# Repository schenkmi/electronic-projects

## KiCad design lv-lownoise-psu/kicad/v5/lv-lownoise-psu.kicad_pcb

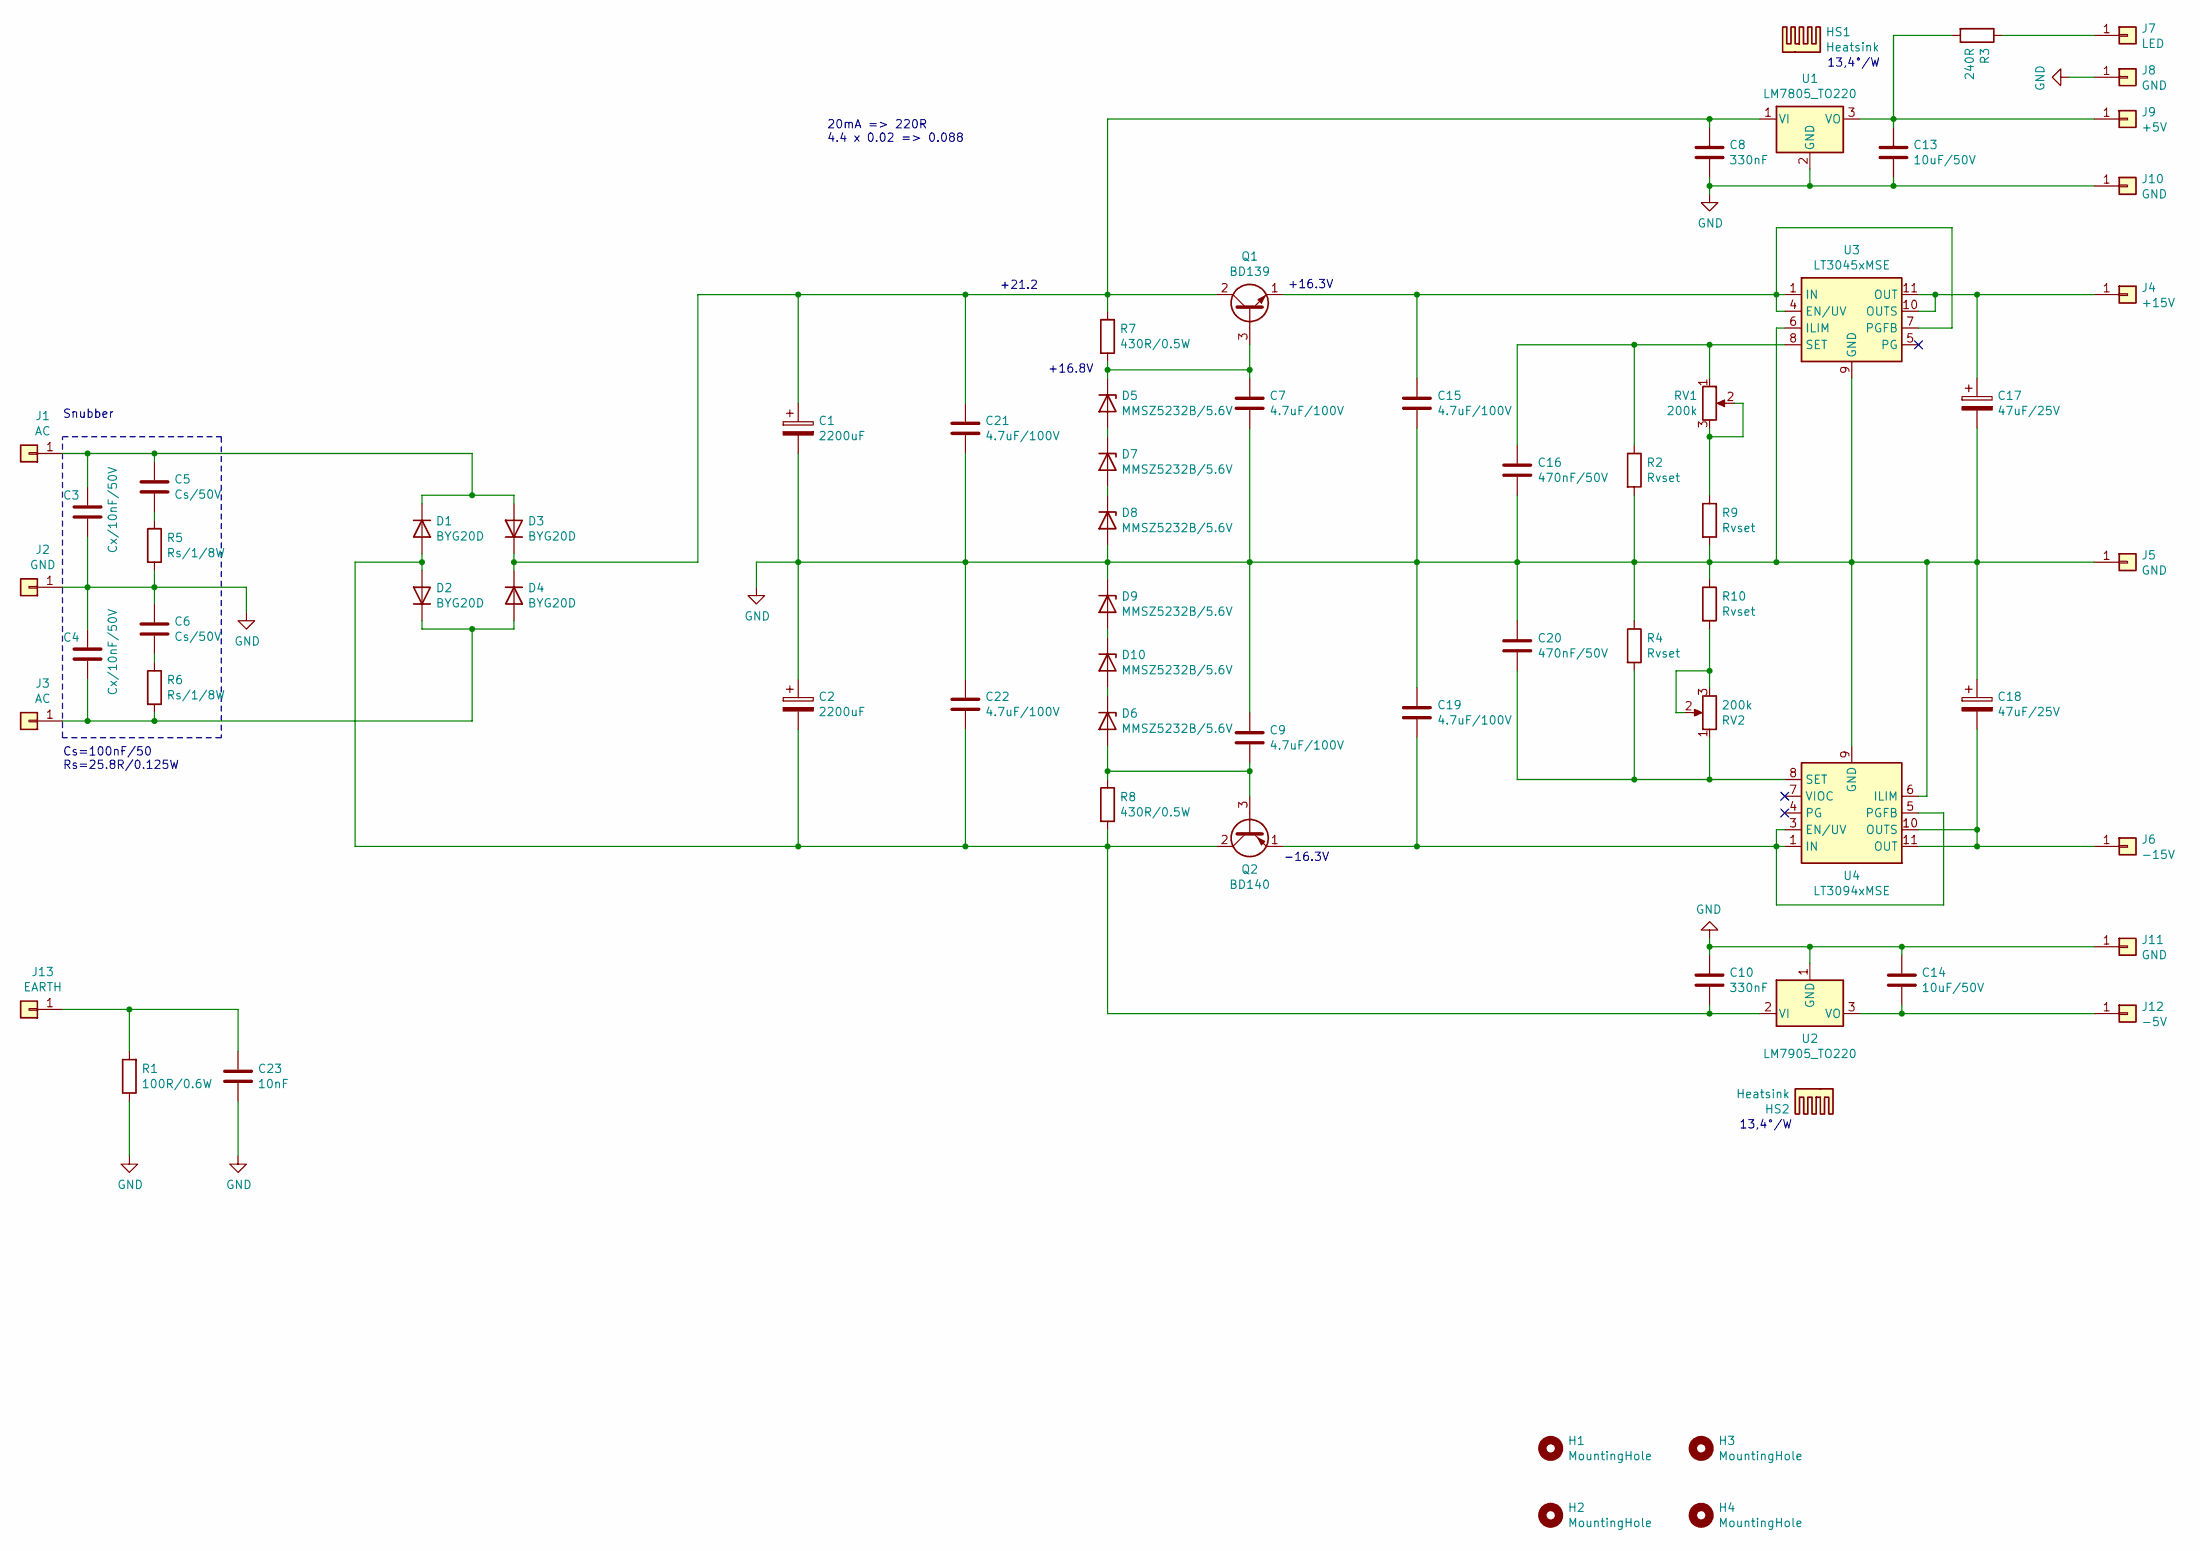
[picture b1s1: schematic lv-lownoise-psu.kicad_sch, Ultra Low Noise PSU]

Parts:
C1, C2: 2200uF; CP_Radial_D16.0mm_P7.50mm
C3, C4: Cx/10nF/50V; C_0805_2012Metric_Pad1.18x1.45mm_HandSolder
C5, C6: Cs/50V; C_0805_2012Metric_Pad1.18x1.45mm_HandSolder
C7, C9, C15, C19, C21, C22: 4.7uF/100V; C_1206_3216Metric_Pad1.33x1.80mm_HandSolder
C8, C10: 330nF; C_0805_2012Metric_Pad1.18x1.45mm_HandSolder
C13, C14: 10uF/50V; C_1210_3225Metric_Pad1.33x2.70mm_HandSolder
C16, C20: 470nF/50V; C_0805_2012Metric_Pad1.18x1.45mm_HandSolder
C17, C18: 47uF/25V; CP_EIA-7343-31_Kemet-D_HandSolder
C23: 10nF; C_Rect_L7.2mm_W2.5mm_P5.00mm_FKS2_FKP2_MKS2_MKP2
D1, D2, D3, D4: BYG20D; D_SMA_Handsoldering
D5, D6, D7, D8, D9, D10: MMSZ5232B/5.6V; D_SOD-123
H1, H2, H3, H4: MountingHole; MountingHole_3.2mm_M3_Pad_Via
HS1, HS2: Heatsink; Heatsink_Fischer_SK104-STC-STIC_35x13mm_2xDrill2.5mm
J1, J3: AC; Pin_D1.3mm_L11.0mm
J2: GND; Pin_D1.3mm_L11.0mm
J4: +15V; Pin_D1.0mm_L10.0mm
J5, J8, J10, J11: GND; Pin_D1.0mm_L10.0mm
J6: -15V; Pin_D1.0mm_L10.0mm
J7: LED; Pin_D1.0mm_L10.0mm
J9: +5V; Pin_D1.0mm_L10.0mm
J12: -5V; Pin_D1.0mm_L10.0mm
J13: EARTH; Pin_D1.3mm_L11.0mm
Q1: BD139; TO-126-3_Vertical
Q2: BD140; TO-126-3_Vertical
R1: 100R/0.6W; R_Axial_DIN0207_L6.3mm_D2.5mm_P10.16mm_Horizontal
R2, R4, R9, R10: Rvset; R_0805_2012Metric_Pad1.20x1.40mm_HandSolder
R3: 240R; R_0805_2012Metric_Pad1.20x1.40mm_HandSolder
R5, R6: Rs/1/8W; R_0805_2012Metric_Pad1.20x1.40mm_HandSolder
R7, R8: 430R/0.5W; R_0805_2012Metric_Pad1.20x1.40mm_HandSolder
RV1, RV2: 200k; Potentiometer_Bourns_3296W_Vertical
U1: LM7805_TO220; TO-220-3_Vertical
U2: LM7905_TO220; TO-220-3_Vertical
U3: LT3045xMSE; MSOP-12-1EP_3x4.039mm_P0.65mm_EP1.651x2.845mm
U4: LT3094xMSE; MSOP-12-1EP_3x4.039mm_P0.65mm_EP1.651x2.845mm

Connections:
GND: C1.2, C2.1, C3.2, C4.1, C6.1, C7.2, C8.2, C9.1, C10.1, C13.2, C14.1, C15.2, C16.2, C17.2, C18.1, C19.1, C20.1, C21.2, C22.1, C23.2, D8.2 (A), D9.1 (K), J2.1, J5.1, J8.1, J10.1, J11.1, R1.1, R2.2, R4.1, R5.2, R9.2, R10.1, U1.2 (GND), U2.1 (GND), U3.6 (ILIM), U3.9 (GND), U3.13 (GND), U4.6 (ILIM), U4.9 (GND)
unnamed: C5.2, R5.1
unnamed: C6.2, R6.1
unnamed: C2.2, C10.2, C22.2, D1.2 (A), D2.2 (A), Q2.2 (C), R8.2, U2.2 (VI)
unnamed: C3.1, C5.1, D1.1 (K), D3.2 (A), J1.1
unnamed: C4.2, D2.1 (K), D4.2 (A), J3.1, R6.2
unnamed: C1.1, C8.1, C21.1, D3.1 (K), D4.1 (K), Q1.2 (C), R7.1, U1.1 (VI)
unnamed: D5.2 (A), D7.1 (K)
unnamed: C7.1, D5.1 (K), Q1.3 (B), R7.2
unnamed: C9.2, D6.2 (A), Q2.3 (B), R8.1
unnamed: D7.2 (A), D8.1 (K)
unnamed: D6.1 (K), D10.2 (A)
unnamed: D9.2 (A), D10.1 (K)
unnamed: C17.1, J4.1, U3.10 (OUTS), U3.11 (OUT), U3.12 (OUT)
unnamed: C18.2, J6.1, U4.10 (OUTS), U4.11 (OUT), U4.12 (OUT)
unnamed: J7.1, R3.1
unnamed: C13.1, J9.1, R3.2, U1.3 (VO)
unnamed: C14.2, J12.1, U2.3 (VO)
unnamed: C23.1, J13.1, R1.2
unnamed: C15.1, Q1.1 (E), U3.1 (IN), U3.2 (IN), U3.3 (IN), U3.4 (EN/UV), U3.7 (PGFB)
unnamed: C19.2, Q2.1 (E), U4.1 (IN), U4.2 (IN), U4.3 (EN/UV), U4.5 (PGFB), U4.13 (IN)
unnamed: R9.1, RV1.2, RV1.3
unnamed: R10.2, RV2.2, RV2.3
unnamed: C16.1, R2.1, RV1.1, U3.8 (SET)
unnamed: C20.2, R4.2, RV2.1, U4.8 (SET)

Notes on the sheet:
+16.3V
13,4°/W
+21.2
Snubber
Cs=100nF/50 Rs=25.8R/0.125W
-16.3V
+16.8V
20mA => 220R 4.4 x 0.02 => 0.088

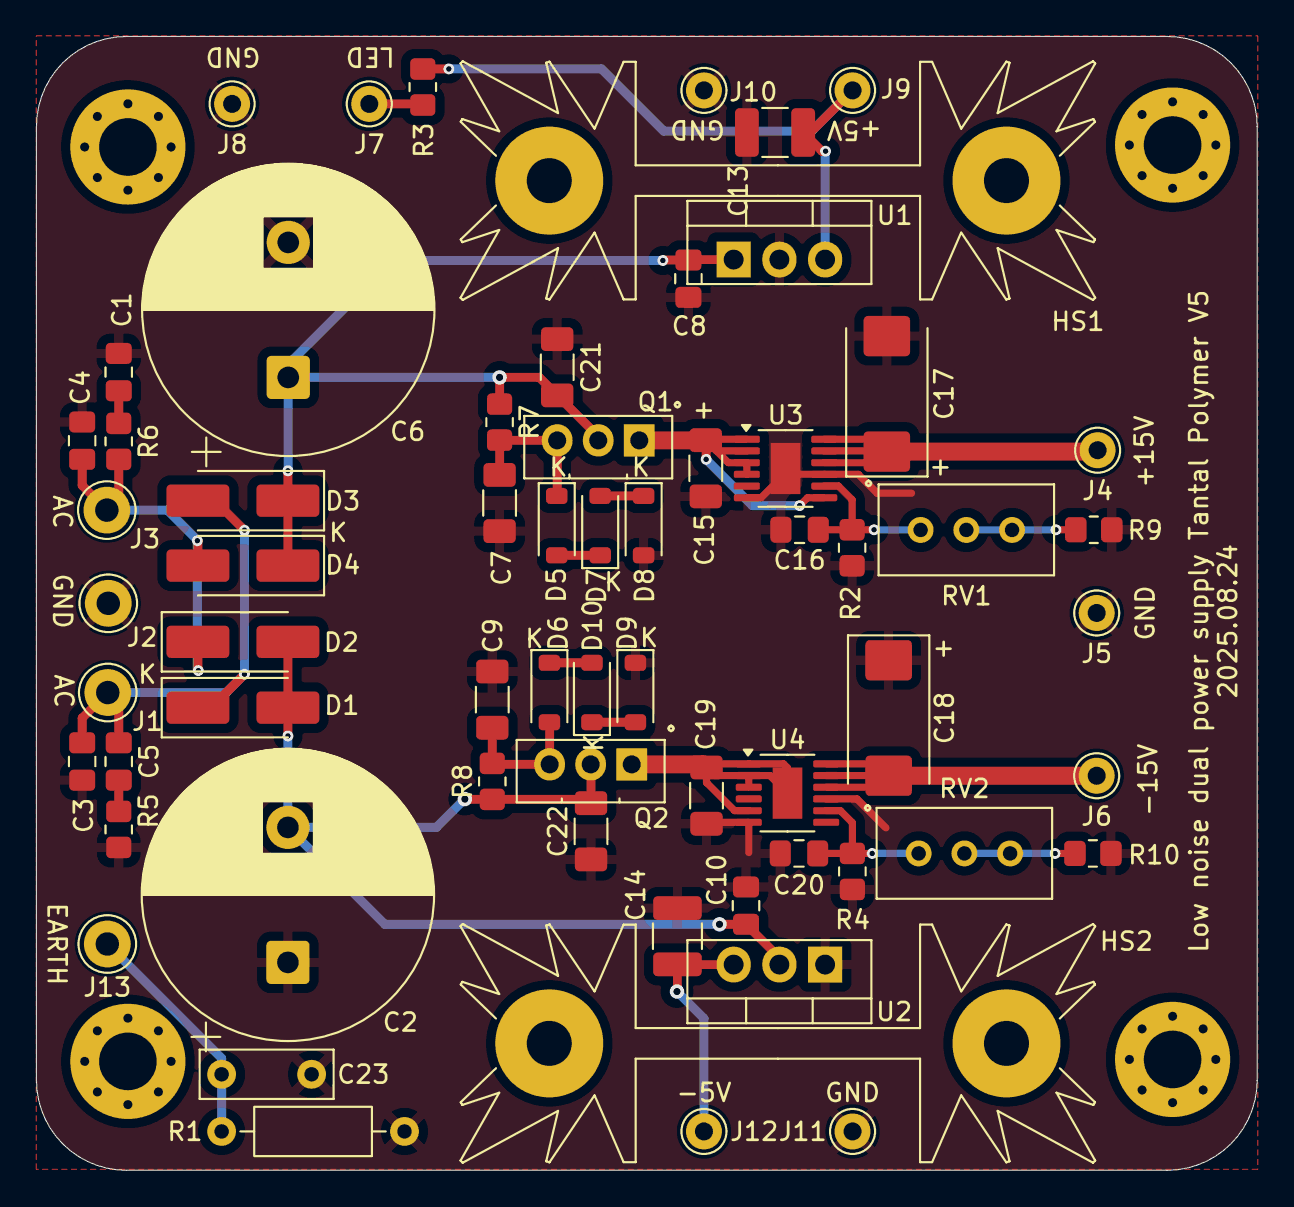
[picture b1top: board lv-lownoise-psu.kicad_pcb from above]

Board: 2 copper layers, 67.8 x 63.0 mm, 68 parts (0 on the bottom side), 25 nets.

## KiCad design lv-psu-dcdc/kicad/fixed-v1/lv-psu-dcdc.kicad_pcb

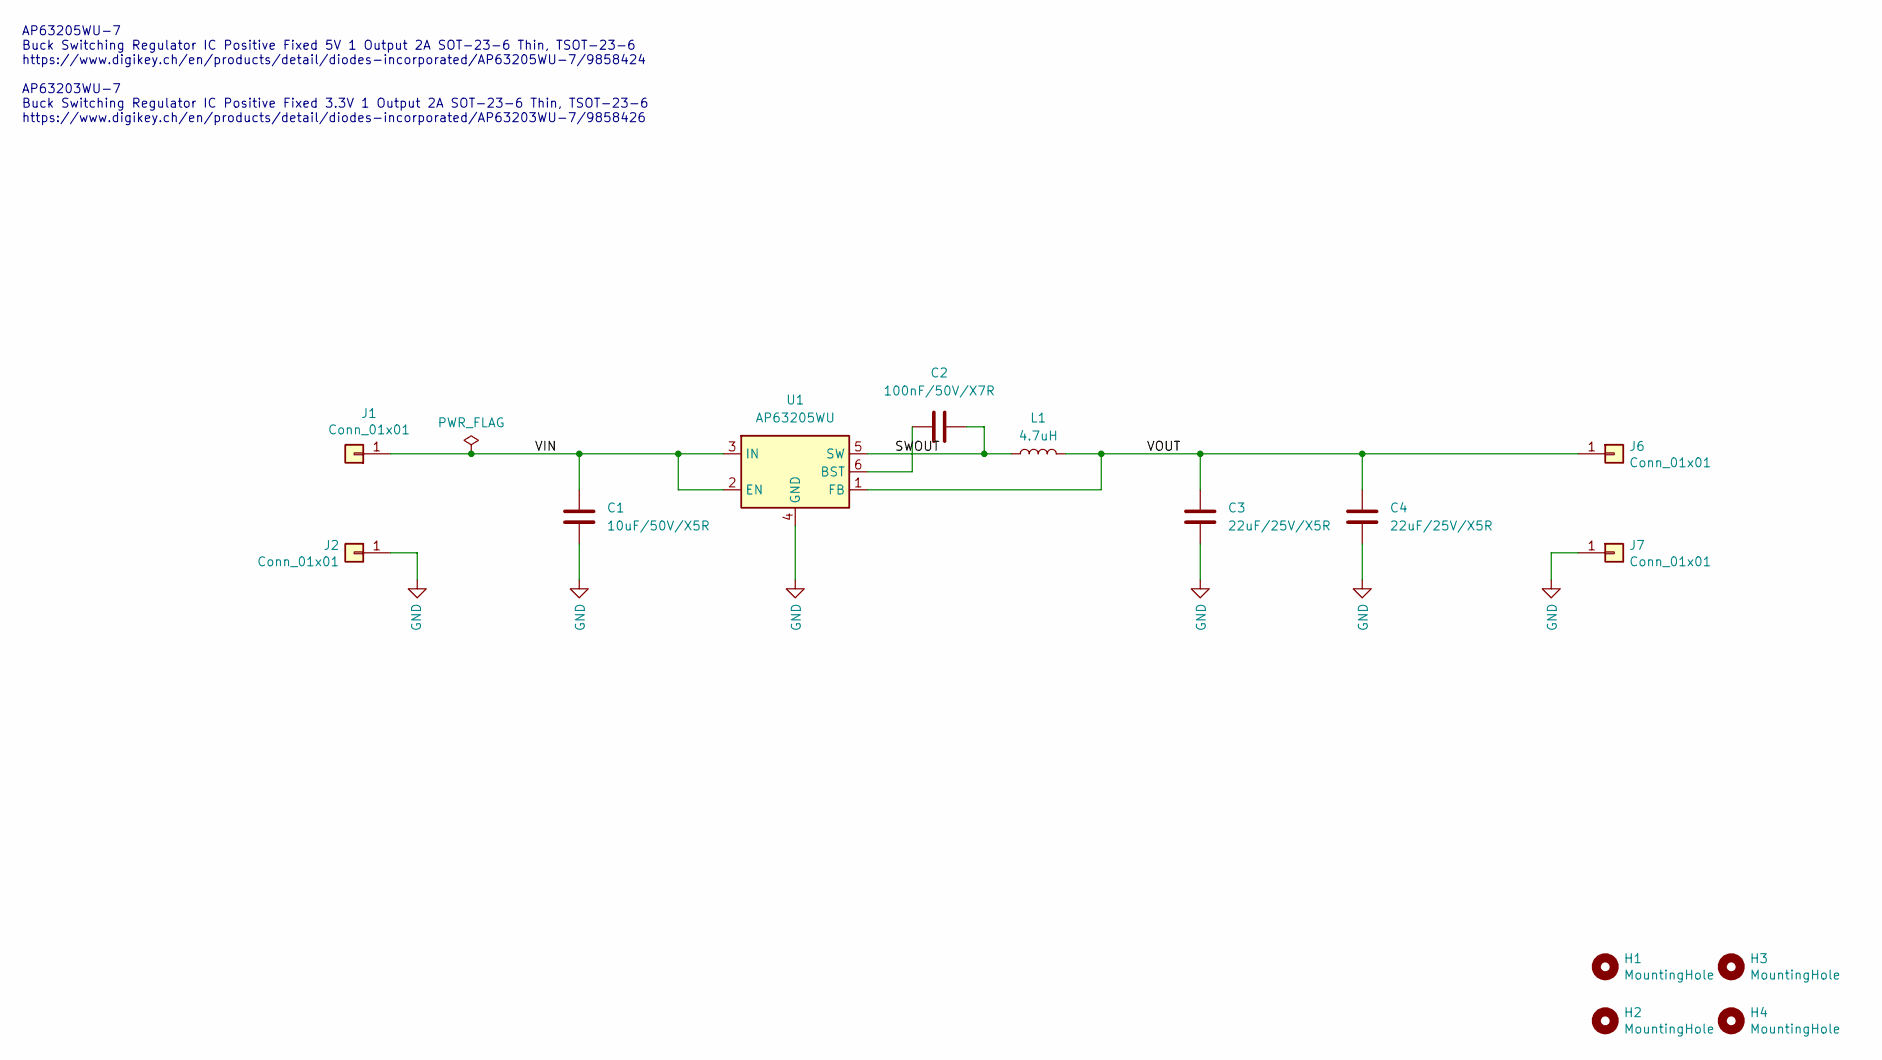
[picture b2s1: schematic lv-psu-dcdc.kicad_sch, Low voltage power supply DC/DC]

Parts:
C1: 10uF/50V/X5R; C_0805_2012Metric_Pad1.18x1.45mm_HandSolder
C2: 100nF/50V/X7R; C_0805_2012Metric_Pad1.18x1.45mm_HandSolder
C3, C4: 22uF/25V/X5R; C_0805_2012Metric_Pad1.18x1.45mm_HandSolder
H1, H2, H3, H4: MountingHole; MountingHole_3.2mm_M3_Pad_Via
J1, J2, J6, J7: Conn_01x01; Pin_D1.0mm_L10.0mm
L1: 4.7uH; L_Bourns-SRN6028
U1: AP63205WU; TSOT-23-6

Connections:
/SWOUT: C2.1, L1.1, U1.5 (SW)
/VIN: C1.1, J1.1, U1.2 (EN), U1.3 (IN)
/VOUT: C3.1, C4.1, J6.1, L1.2, U1.1 (FB)
GND: C1.2, C3.2, C4.2, J2.1, J7.1, U1.4 (GND)
unnamed: C2.2, U1.6 (BST)

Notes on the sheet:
AP63205WU-7 Buck Switching Regulator IC Positive Fixed 5V 1 Output 2A SOT-23-6 Thin, TSOT-23-6 https://www.digikey.ch/en/products/detail/diodes-incorporated/AP63205WU-7/9858424 AP63203WU-7 Buck Switching Regulator IC Positive Fixed 3.3V 1 Output 2A SOT-23-6 Thin, TSOT-23-6 https://www.digikey.ch/en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

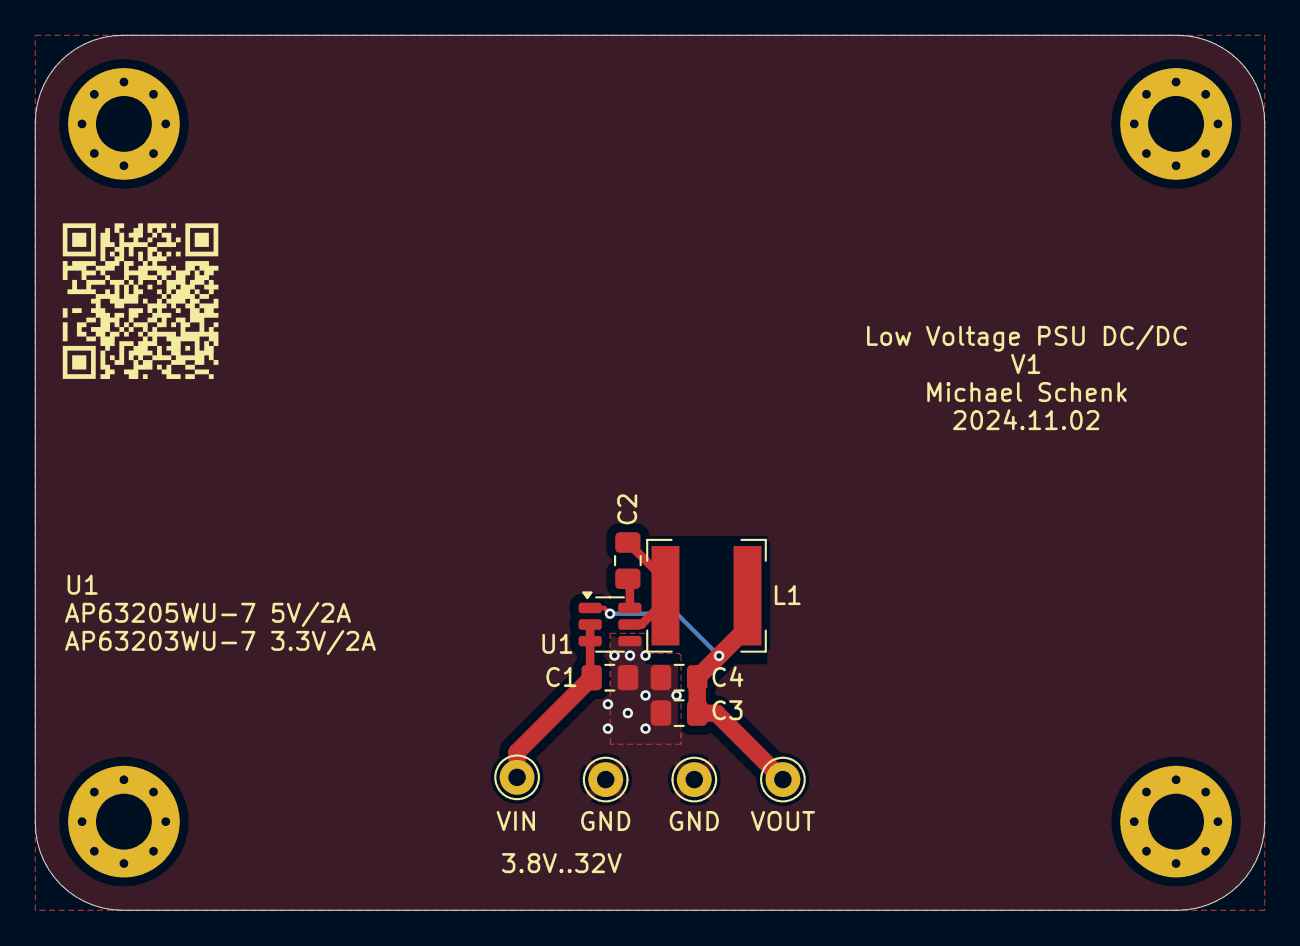
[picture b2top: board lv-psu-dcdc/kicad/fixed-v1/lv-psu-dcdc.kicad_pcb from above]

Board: 2 copper layers, 70.5 x 50.2 mm, 14 parts (0 on the bottom side), 5 nets.

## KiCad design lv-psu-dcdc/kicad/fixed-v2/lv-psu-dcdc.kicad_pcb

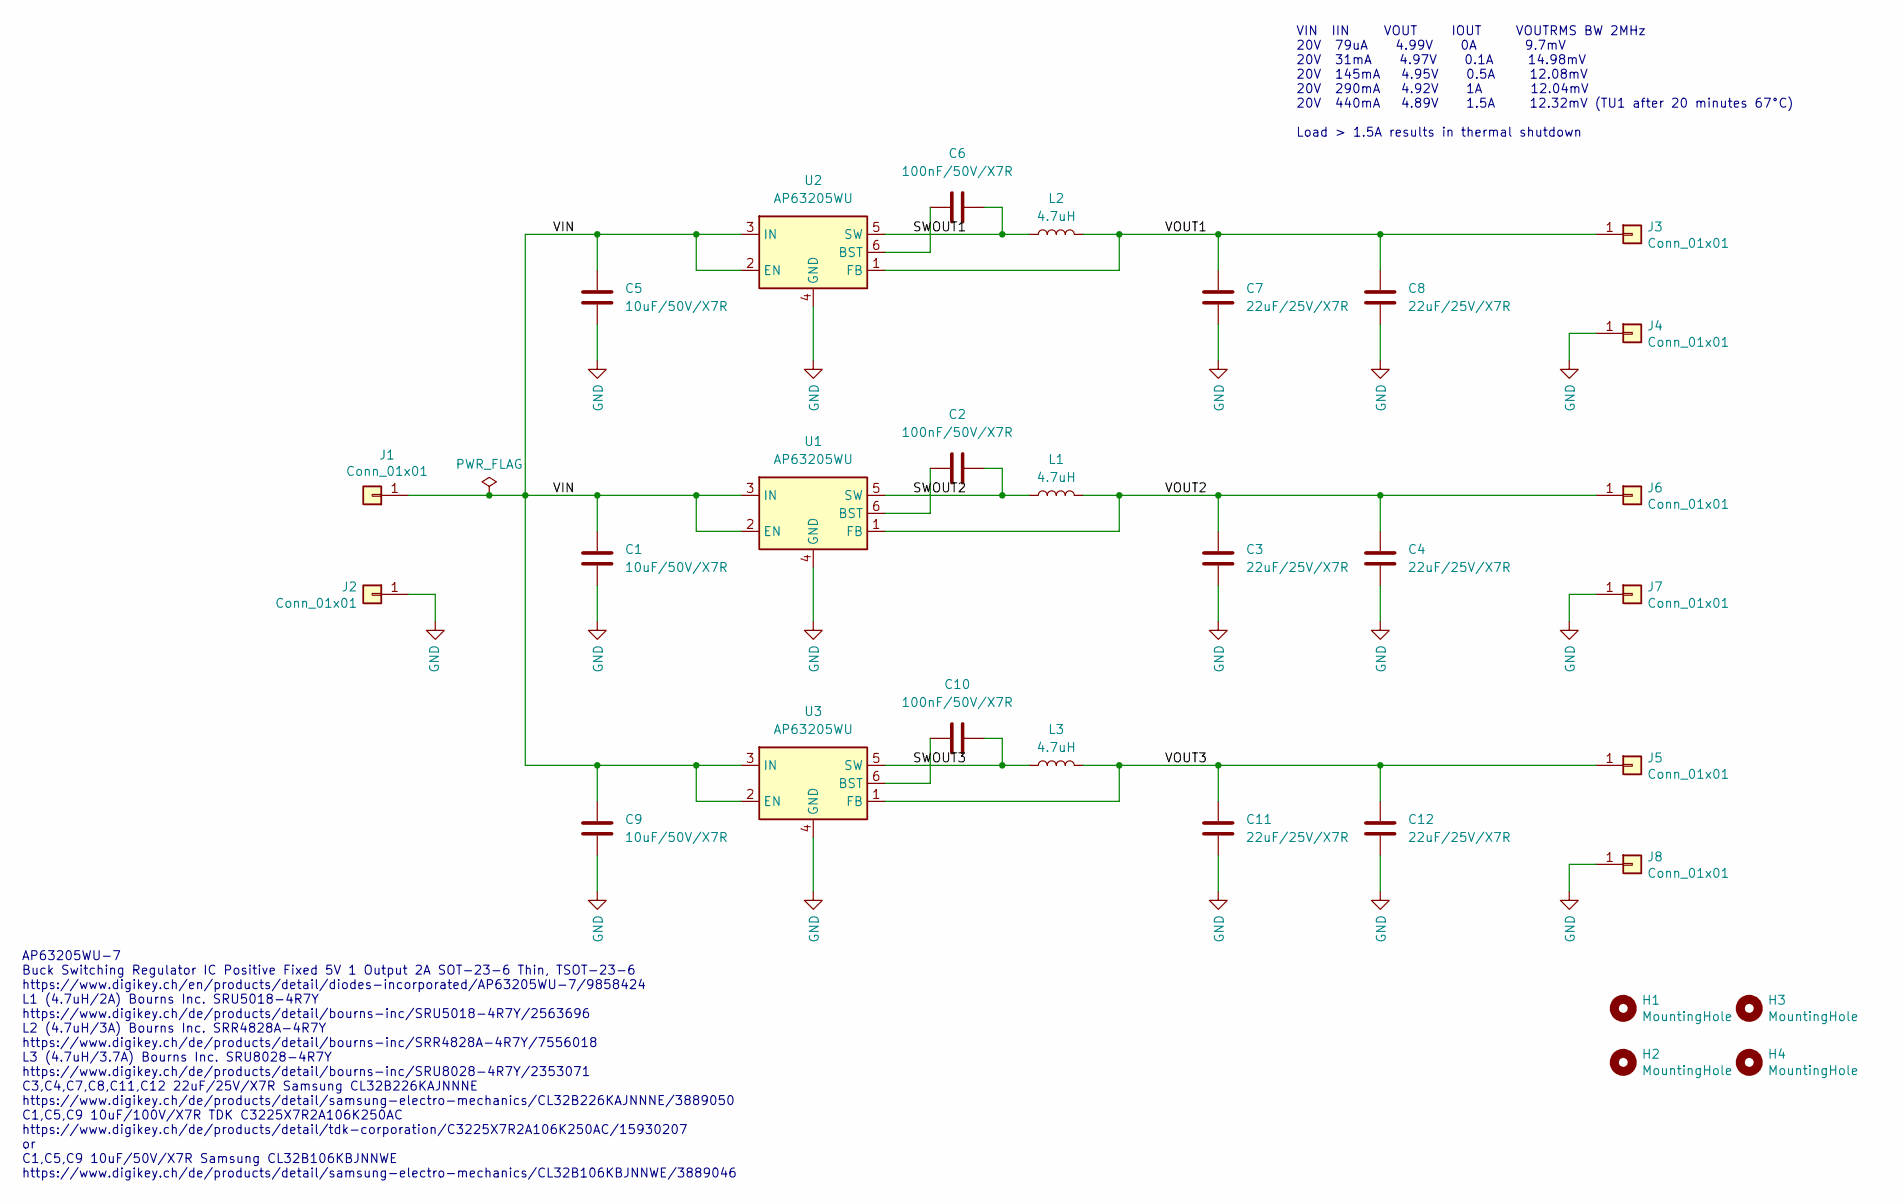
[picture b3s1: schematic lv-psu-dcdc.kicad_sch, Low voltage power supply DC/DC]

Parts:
C1, C5, C9: 10uF/50V/X7R; C_1210_3225Metric_Pad1.33x2.70mm_HandSolder
C2, C6, C10: 100nF/50V/X7R; C_0805_2012Metric_Pad1.18x1.45mm_HandSolder
C3, C4, C7, C8, C11, C12: 22uF/25V/X7R; C_1210_3225Metric_Pad1.33x2.70mm_HandSolder
H1, H2, H3, H4: MountingHole; MountingHole_3.2mm_M3_Pad_Via
J1, J2, J3, J4, J5, J6, J7, J8: Conn_01x01; Pin_D1.0mm_L10.0mm
L1: 4.7uH; L_Bourns_SRU5016_5.2x5.2mm
L2: 4.7uH; IND_SRR4828A
L3: 4.7uH; L_Bourns-SRU8028_8.0x8.0mm
U1, U2, U3: AP63205WU; TSOT-23-6

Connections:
/SWOUT1: C6.1, L2.1, U2.5 (SW)
/SWOUT2: C2.1, L1.1, U1.5 (SW)
/SWOUT3: C10.1, L3.1, U3.5 (SW)
/VIN: C1.1, C5.1, C9.1, J1.1, U1.2 (EN), U1.3 (IN), U2.2 (EN), U2.3 (IN), U3.2 (EN), U3.3 (IN)
/VOUT1: C7.1, C8.1, J3.1, L2.2, U2.1 (FB)
/VOUT2: C3.1, C4.1, J6.1, L1.2, U1.1 (FB)
/VOUT3: C11.1, C12.1, J5.1, L3.2, U3.1 (FB)
GND: C1.2, C3.2, C4.2, C5.2, C7.2, C8.2, C9.2, C11.2, C12.2, J2.1, J4.1, J7.1, J8.1, U1.4 (GND), U2.4 (GND), U3.4 (GND)
unnamed: C2.2, U1.6 (BST)
unnamed: C6.2, U2.6 (BST)
unnamed: C10.2, U3.6 (BST)

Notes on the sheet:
AP63205WU-7 Buck Switching Regulator IC Positive Fixed 5V 1 Output 2A SOT-23-6 Thin, TSOT-23-6 https://www.digikey.ch/en/products/detail/diodes-incorporated/AP63205WU-7/9858424 L1 (4.7uH/2A) Bourns Inc. SRU5018-4R7Y https://www.digikey.ch/de/products/detail/bourns-inc/SRU5018-4R7Y/2563696 L2 (4.7uH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
VIN IIN VOUT IOUT VOUTRMS BW 2MHz 20V 79uA 4.99V 0A 9.7mV 20V 31mA 4.97V 0.1A 14.98mV 20V 145mA 4.95V 0.5A 12.08mV 20V 290mA 4.92V 1A 12.04mV 20V 440mA 4.89V 1.5A 12.32mV (TU1 after 20 minutes 67°C) Load > 1.5A results in thermal shutdown

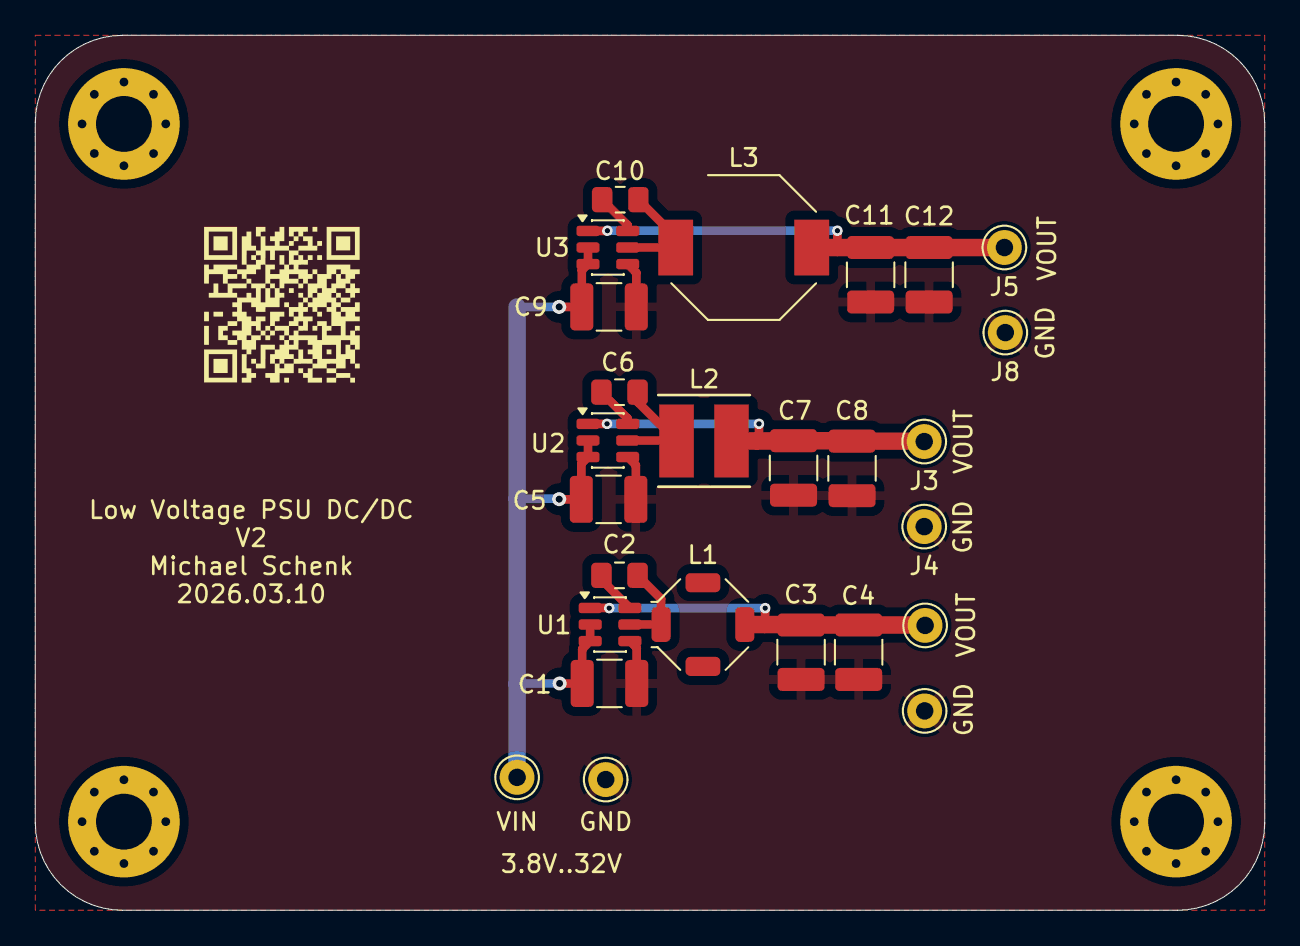
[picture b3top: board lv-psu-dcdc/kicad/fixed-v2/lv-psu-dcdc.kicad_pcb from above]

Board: 2 copper layers, 70.5 x 50.2 mm, 30 parts (0 on the bottom side), 11 nets.

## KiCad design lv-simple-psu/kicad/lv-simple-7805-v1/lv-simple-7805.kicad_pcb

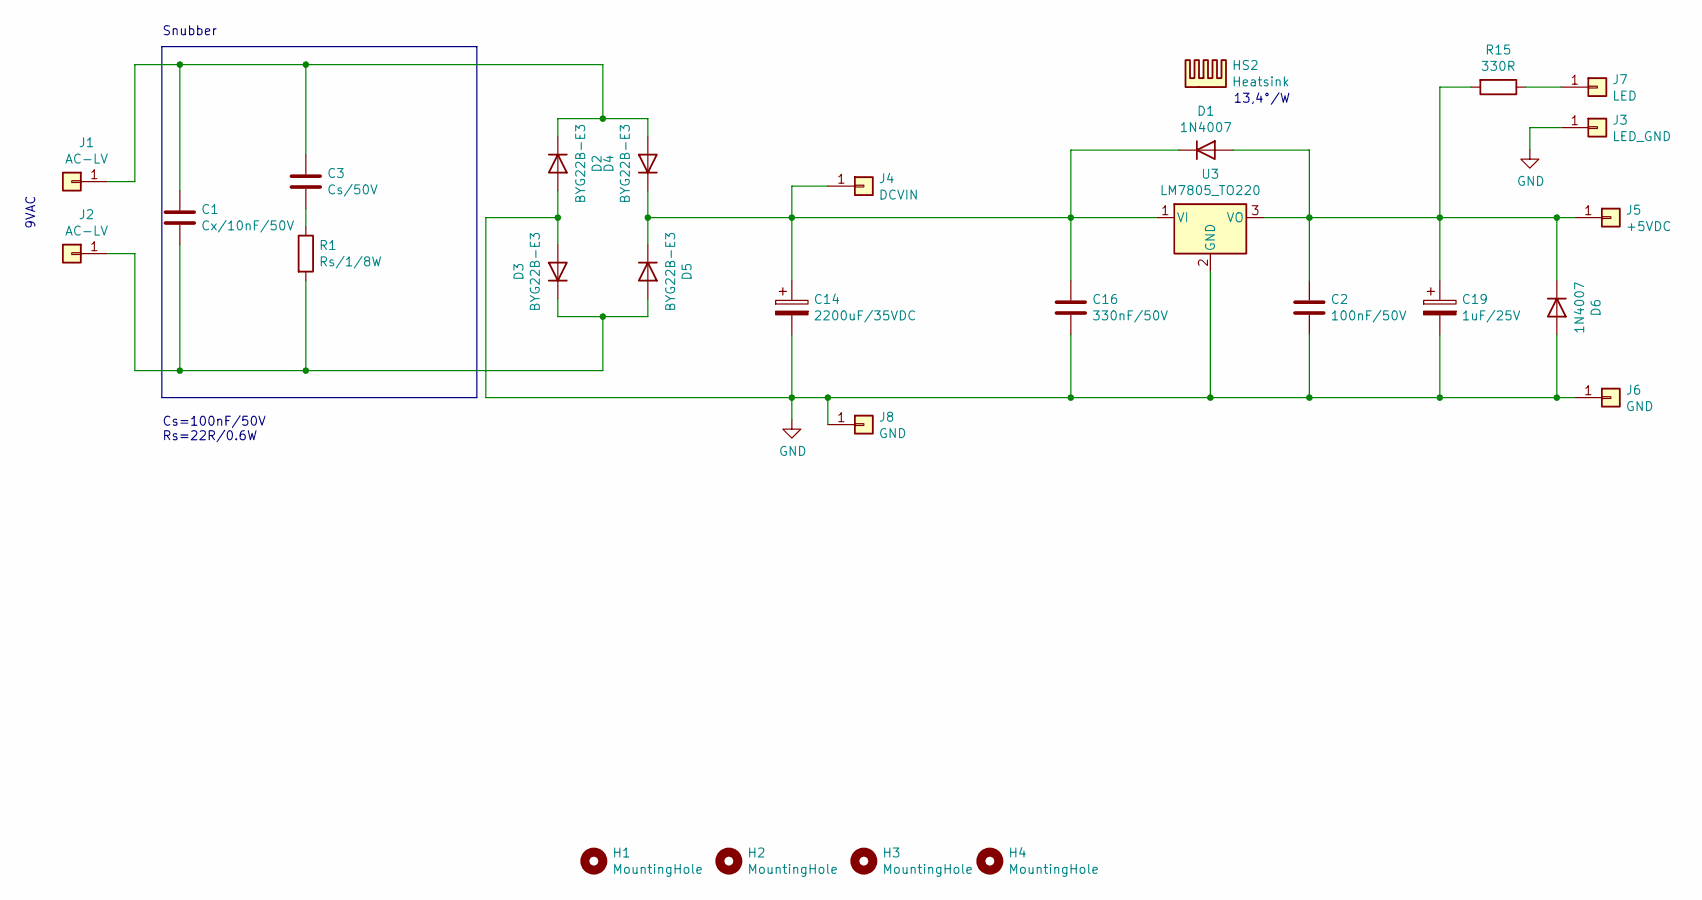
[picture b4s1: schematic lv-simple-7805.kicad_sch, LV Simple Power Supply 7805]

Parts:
C1: Cx/10nF/50V; C_0805_2012Metric_Pad1.18x1.45mm_HandSolder
C2: 100nF/50V; C_0805_2012Metric_Pad1.18x1.45mm_HandSolder
C3: Cs/50V; C_0805_2012Metric_Pad1.18x1.45mm_HandSolder
C14: 2200uF/35VDC; CP_Radial_D16.0mm_P7.50mm
C16: 330nF/50V; C_0805_2012Metric_Pad1.18x1.45mm_HandSolder
C19: 1uF/25V; CP_Radial_D5.0mm_P2.00mm
D1, D6: 1N4007; D_SMA_Handsoldering
D2, D3, D4, D5: BYG22B-E3; D_SMA_Handsoldering
H1, H2, H3, H4: MountingHole; MountingHole_3.2mm_M3
HS2: Heatsink; Heatsink_Fischer_SK104-STC-STIC_35x13mm_2xDrill2.5mm
J1, J2: AC-LV; Pin_D1.0mm_L10.0mm
J3: LED_GND; Pin_D1.0mm_L10.0mm
J4: DCVIN; Pin_D1.0mm_L10.0mm
J5: +5VDC; Pin_D1.0mm_L10.0mm
J6, J8: GND; Pin_D1.0mm_L10.0mm
J7: LED; Pin_D1.0mm_L10.0mm
R1: Rs/1/8W; R_0805_2012Metric_Pad1.20x1.40mm_HandSolder
R15: 330R; R_0805_2012Metric_Pad1.20x1.40mm_HandSolder
U3: LM7805_TO220; TO-220-3_Vertical

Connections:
GND: C2.2, C14.2, C16.2, C19.2, D2.2 (A), D3.2 (A), D6.2 (A), J3.1, J6.1, J8.1, U3.2 (GND)
unnamed: C1.1, C3.1, D2.1 (K), D4.2 (A), J1.1
unnamed: C1.2, D3.1 (K), D5.2 (A), J2.1, R1.2
unnamed: C3.2, R1.1
unnamed: C14.1, C16.1, D1.1 (K), D4.1 (K), D5.1 (K), J4.1, U3.1 (VI)
unnamed: J7.1, R15.1
unnamed: C2.1, C19.1, D1.2 (A), D6.1 (K), J5.1, R15.2, U3.3 (VO)

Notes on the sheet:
Snubber
9VAC
13,4°/W
Cs=100nF/50V Rs=22R/0.6W

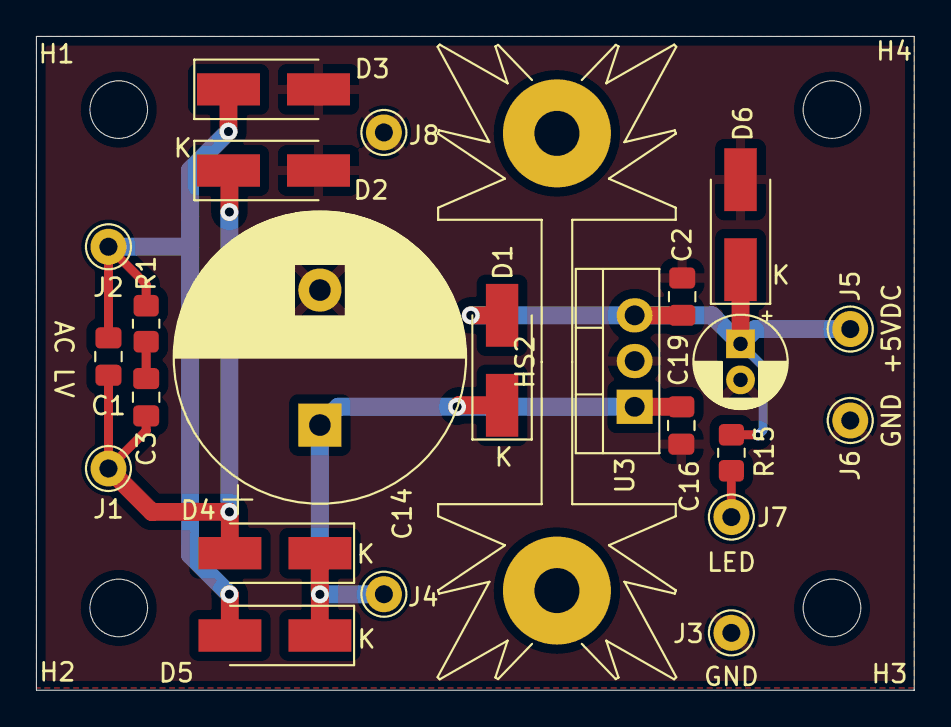
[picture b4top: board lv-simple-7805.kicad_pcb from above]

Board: 2 copper layers, 48.8 x 36.3 mm, 28 parts (0 on the bottom side), 7 nets.
